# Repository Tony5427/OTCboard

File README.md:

# OTCboard

https://www.ckassoc.com/press-release/how-to-replace-a-hall-effect-sensor-with-a-tmr-sensor

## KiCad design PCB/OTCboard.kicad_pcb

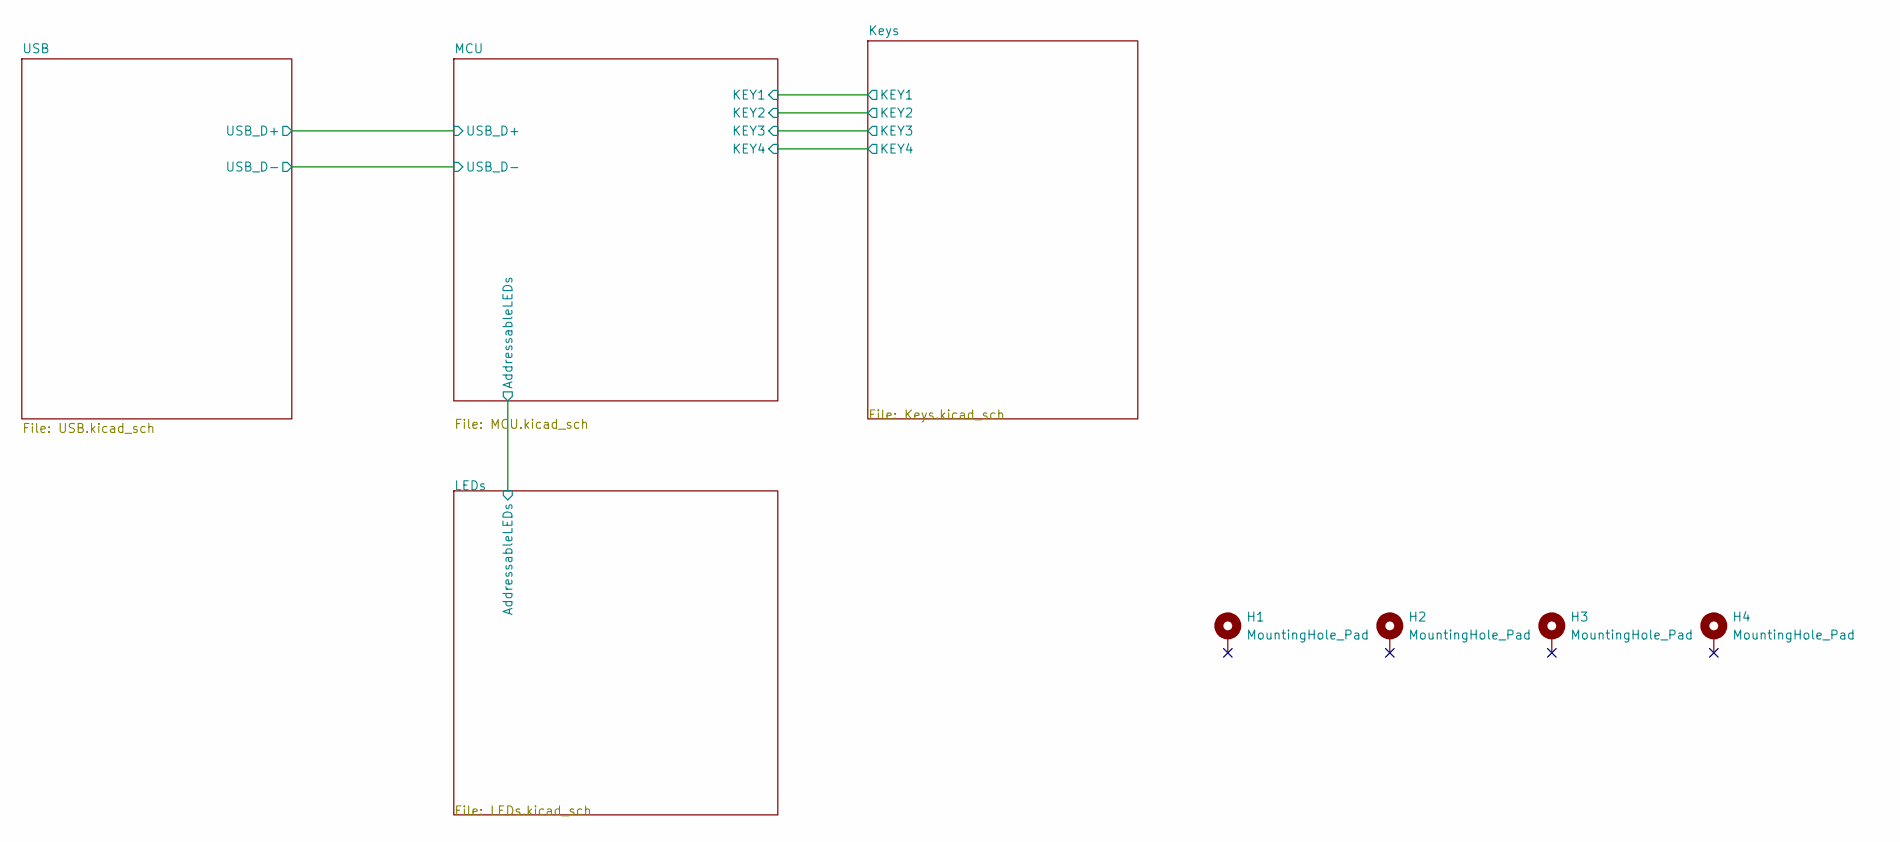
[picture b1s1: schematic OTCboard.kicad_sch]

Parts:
H1, H2, H3, H4: MountingHole_Pad; MountingHole_3.2mm_M3_Pad_TopBottom

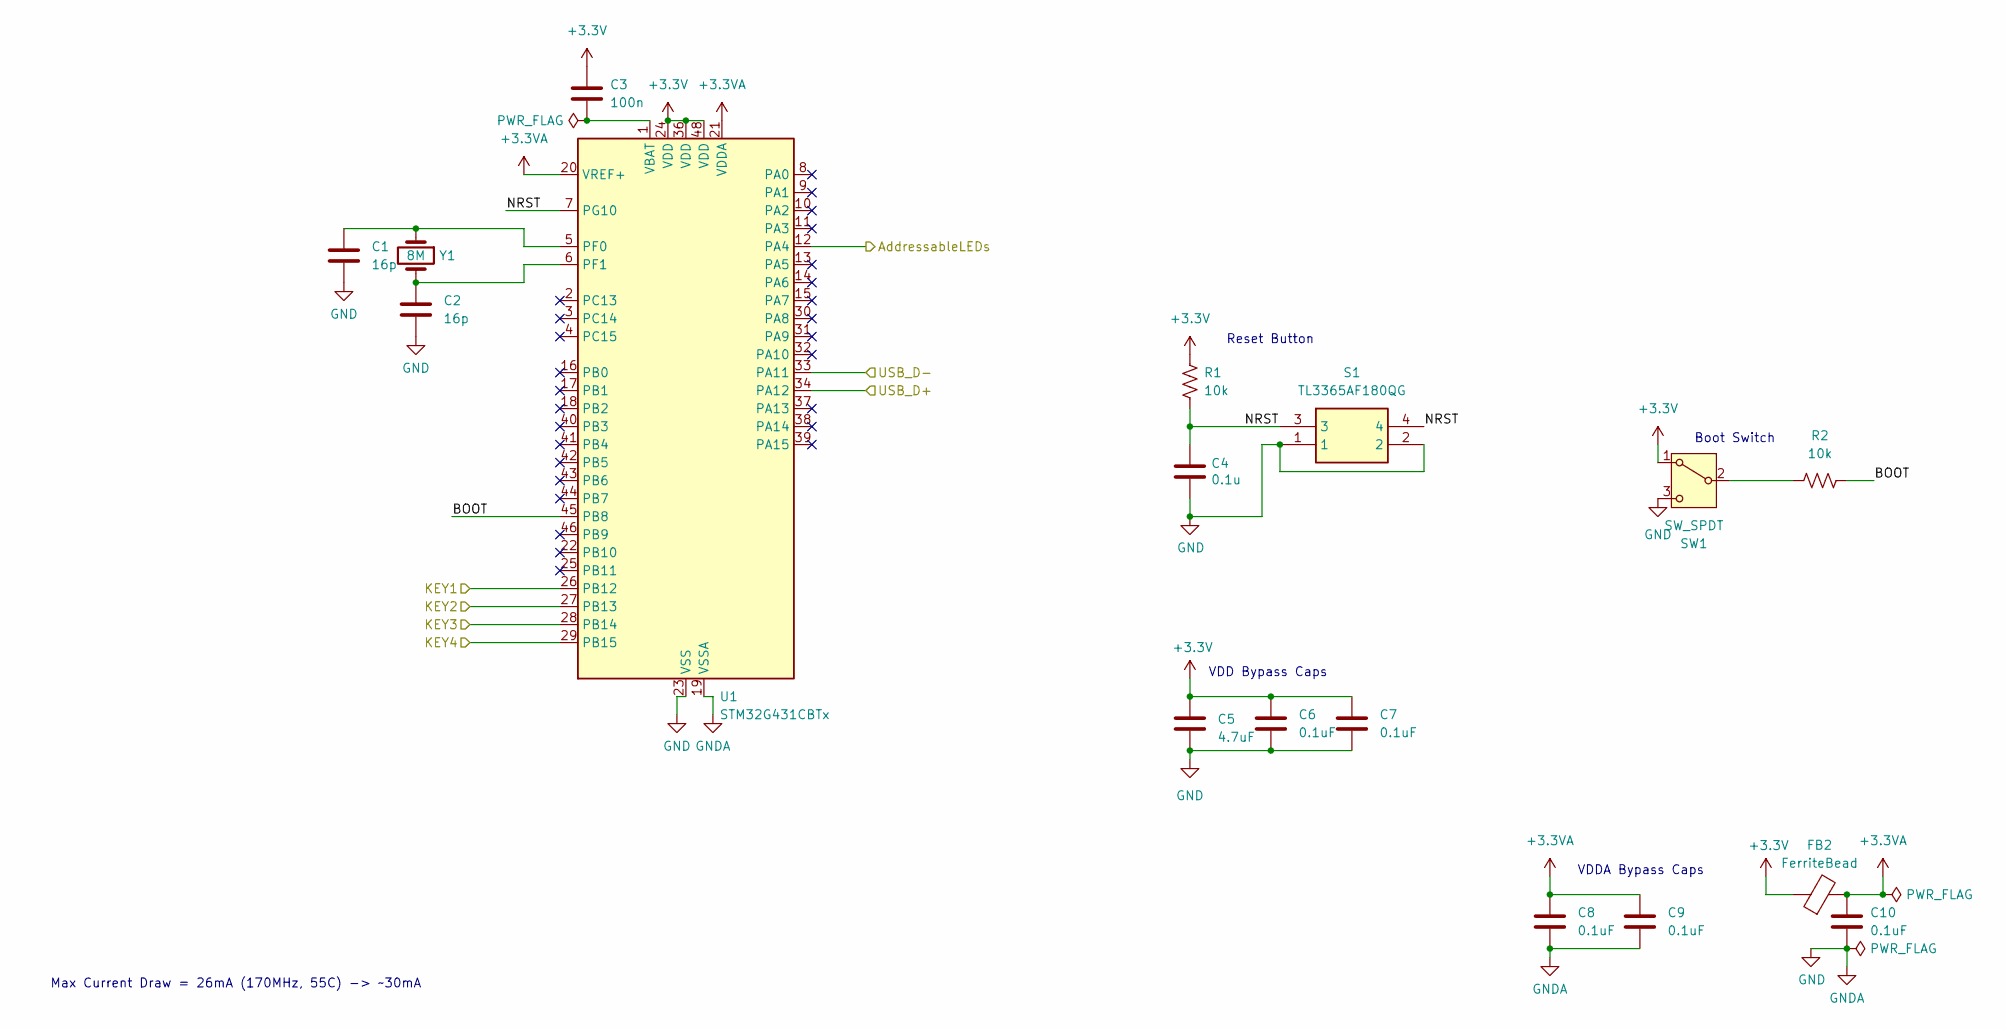
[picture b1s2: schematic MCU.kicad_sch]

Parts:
C1, C2: 16p; C_0603_1608Metric_Pad1.08x0.95mm_HandSolder
C3: 100n; C_0603_1608Metric_Pad1.08x0.95mm_HandSolder
C4: 0.1u; C_0603_1608Metric_Pad1.08x0.95mm_HandSolder; Mouser Part Number MLASH168SB7104KTNA01
C5: 4.7uF; C_0805_2012Metric_Pad1.18x1.45mm_HandSolder; Mouser Part Number 08055D475KAT4A
C6, C7, C8, C9, C10: 0.1uF; C_0603_1608Metric_Pad1.08x0.95mm_HandSolder; Mouser Part Number MLASH168SB7104KTNA01
FB2: FerriteBead; L_0603_1608Metric_Pad1.05x0.95mm_HandSolder; Mouser Part Number 704-MFBW1V2012-121-R
R1, R2: 10k; R_0603_1608Metric_Pad0.98x0.95mm_HandSolder; Mouser Part Number CRCW060310K0FKEI
S1: TL3365AF180QG; Mouser Part Number 612-TL3365AF180QG
SW1: SW_SPDT; CLSB12B01T; Mouser Part Number CJS-1200TA
U1: STM32G431CBTx; LQFP-48_7x7mm_P0.5mm
Y1: 8M; Crystal_SMD_Abracon_ABM3-2Pin_5.0x3.2mm; Mouser Part Number ABM3-8.000MHZ-D2Y-T

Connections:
+3.3V: C3.2, C5.1, C6.1, C7.1, FB2.1, R1.2, SW1.1 (A), U1.24 (VDD), U1.36 (VDD), U1.48 (VDD); also elsewhere on the board
+3.3VA: C8.1, C9.1, C10.1, FB2.2, U1.20 (VREF+), U1.21 (VDDA); also elsewhere on the board
/Keys/KEY1: U1.26 (PB12); also elsewhere on the board
/Keys/KEY2: U1.27 (PB13); also elsewhere on the board
/Keys/KEY3: U1.28 (PB14); also elsewhere on the board
/Keys/KEY4: U1.29 (PB15); also elsewhere on the board
/LEDs/AddressableLEDs: U1.12 (PA4); also elsewhere on the board
/MCU/BOOT: R2.1, U1.45 (PB8)
/MCU/NRST: C4.1, R1.1, S1.3, S1.4, U1.7 (PG10)
/USB/USB_D+: U1.34 (PA12); also elsewhere on the board
/USB/USB_D-: U1.33 (PA11); also elsewhere on the board
GND: C1.2, C2.1, C4.2, C5.2, C6.2, C7.2, C8.2, C9.2, C10.2, S1.1, S1.2, SW1.3 (C), U1.19 (VSSA), U1.23 (VSS), U1.35 (VSS), U1.47 (VSS); also elsewhere on the board
unnamed: R2.2, SW1.2 (B)
unnamed: C1.1, U1.5 (PF0), Y1.1
unnamed: C2.2, U1.6 (PF1), Y1.2
unnamed: C3.1, U1.1 (VBAT)

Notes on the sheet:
Reset Button
VDDA Bypass Caps
VDD Bypass Caps
Boot Switch
Max Current Draw = 26mA (170MHz, 55C) -> ~30mA

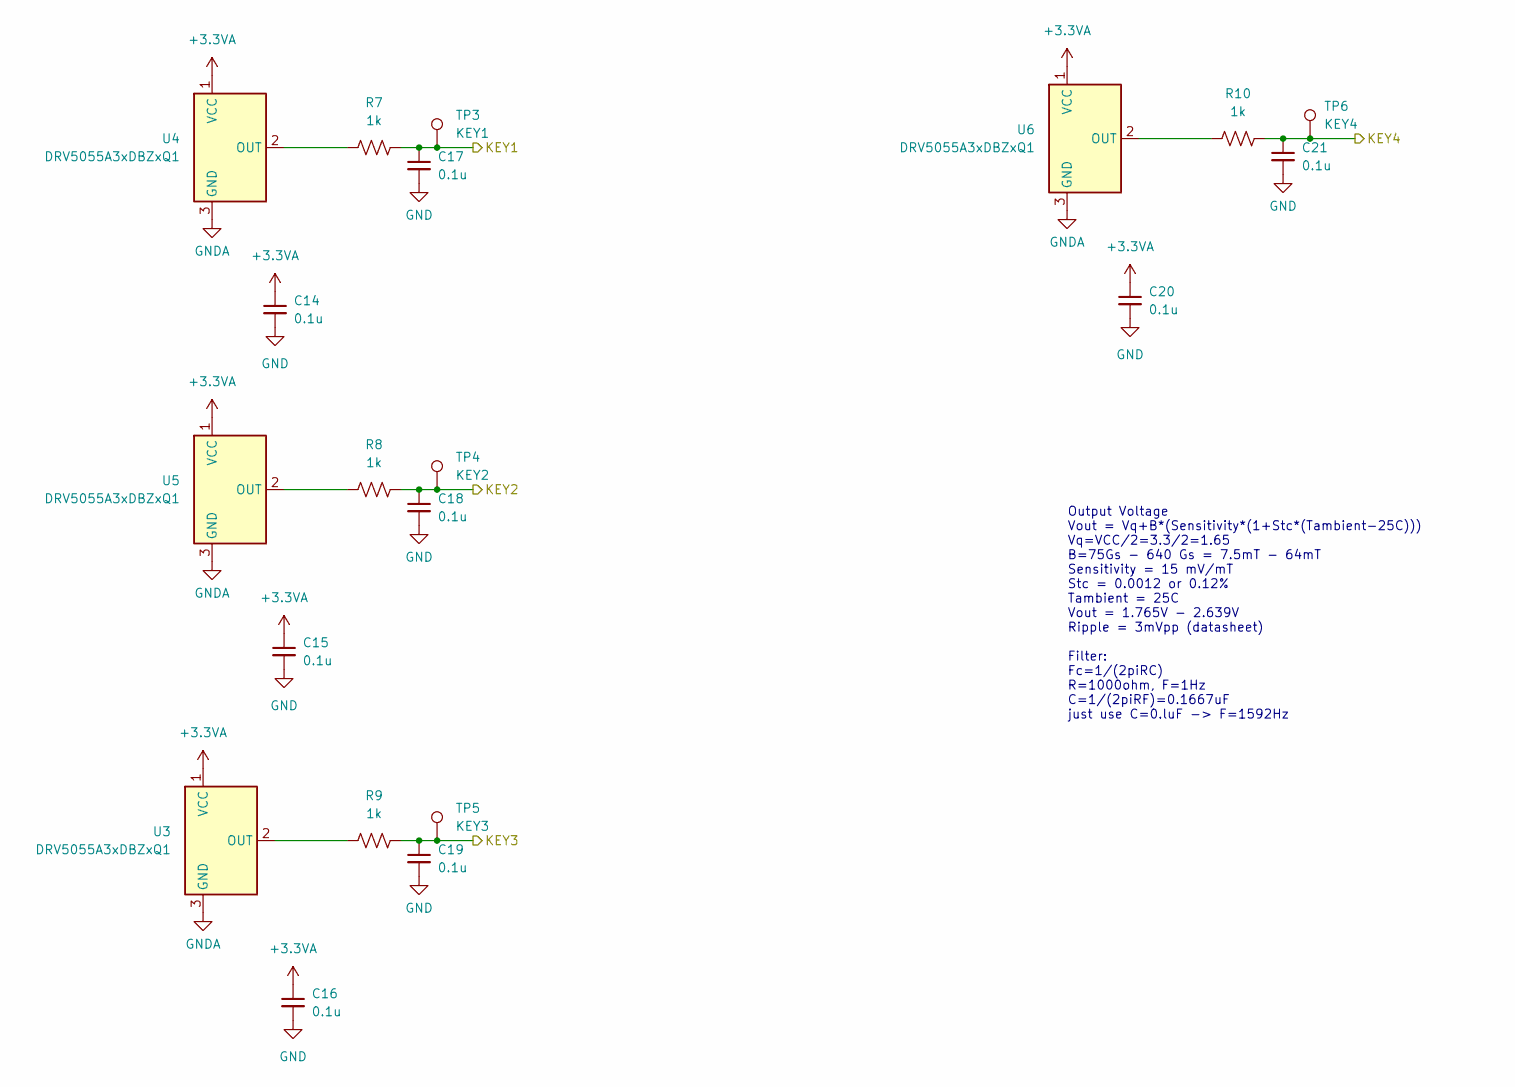
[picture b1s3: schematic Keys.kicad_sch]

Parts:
C14, C15, C16, C17, C18, C19, C20, C21: 0.1u; C_0603_1608Metric_Pad1.08x0.95mm_HandSolder
R7, R8, R9, R10: 1k; R_0603_1608Metric_Pad0.98x0.95mm_HandSolder
TP3: KEY1; TestPoint_Loop_D2.54mm_Drill1.5mm_Beaded
TP4: KEY2; TestPoint_Loop_D2.54mm_Drill1.5mm_Beaded
TP5: KEY3; TestPoint_Loop_D2.54mm_Drill1.5mm_Beaded
TP6: KEY4; TestPoint_Loop_D2.54mm_Drill1.5mm_Beaded
U3, U4, U5, U6: DRV5055A3xDBZxQ1; SOT-23

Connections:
+3.3VA: C14.1, C15.1, C16.1, C20.1, U3.1 (VCC), U4.1 (VCC), U5.1 (VCC), U6.1 (VCC); also elsewhere on the board
/Keys/KEY1: C17.1, R7.2, TP3.1; also elsewhere on the board
/Keys/KEY2: C18.1, R8.2, TP4.1; also elsewhere on the board
/Keys/KEY3: C19.1, R9.2, TP5.1; also elsewhere on the board
/Keys/KEY4: C21.1, R10.2, TP6.1; also elsewhere on the board
GND: C14.2, C15.2, C16.2, C17.2, C18.2, C19.2, C20.2, C21.2, U3.3 (GND), U4.3 (GND), U5.3 (GND), U6.3 (GND); also elsewhere on the board
unnamed: R9.1, U3.2 (OUT)
unnamed: R7.1, U4.2 (OUT)
unnamed: R8.1, U5.2 (OUT)
unnamed: R10.1, U6.2 (OUT)

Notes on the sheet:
Output Voltage Vout = Vq+B*(Sensitivity*(1+Stc*(Tambient-25C))) Vq=VCC/2=3.3/2=1.65 B=75Gs - 640 Gs = 7.5mT - 64mT Sensitivity = 15 mV/mT Stc = 0.0012 or 0.12% Tambient = 25C Vout = 1.765V - 2.639V Ripple = 3mVpp (datasheet) Filter: Fc=1/(2piRC) R=1000ohm, F=1Hz C=1/(2piRF)=0.1667uF just use C=0.lu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

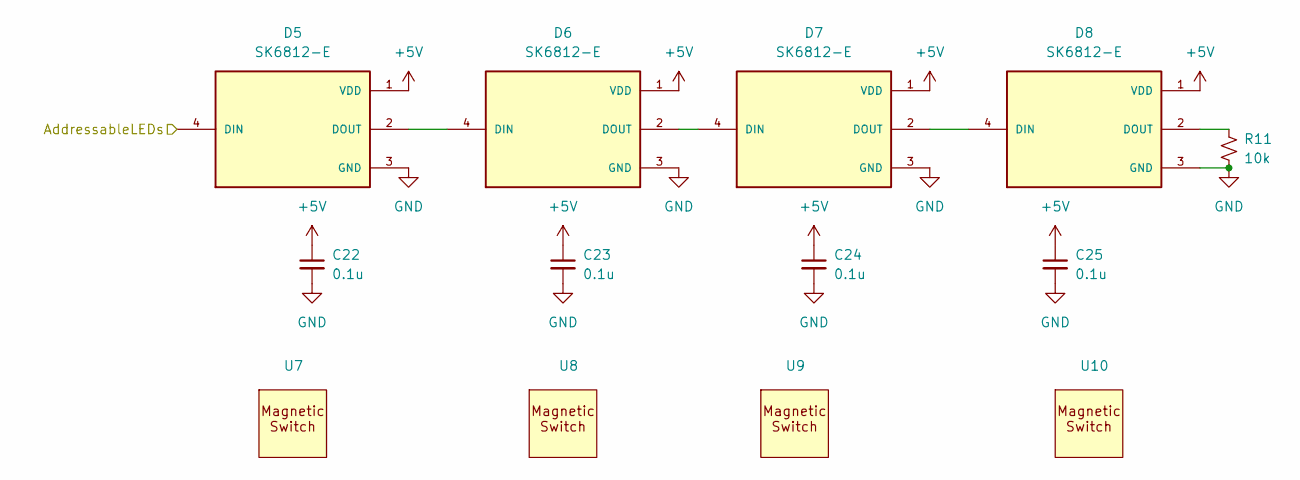
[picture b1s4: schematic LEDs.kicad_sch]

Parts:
C22, C23, C24, C25: 0.1u; C_0603_1608Metric_Pad1.08x0.95mm_HandSolder
D5, D6, D7, D8: SK6812-E; LED_SK6812-E; PARTREV 2
R11: 10k; R_0603_1608Metric_Pad0.98x0.95mm_HandSolder
U7, U8, U9, U10: Cherry MX compatible

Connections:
+5V: C22.1, C23.1, C24.1, C25.1, D5.1 (VDD), D6.1 (VDD), D7.1 (VDD), D8.1 (VDD); also elsewhere on the board
/LEDs/AddressableLEDs: D5.4 (DIN); also elsewhere on the board
GND: C22.2, C23.2, C24.2, C25.2, D5.3 (GND), D6.3 (GND), D7.3 (GND), D8.3 (GND), R11.2; also elsewhere on the board
unnamed: D5.2 (DOUT), D6.4 (DIN)
unnamed: D6.2 (DOUT), D7.4 (DIN)
unnamed: D7.2 (DOUT), D8.4 (DIN)
unnamed: D8.2 (DOUT), R11.1

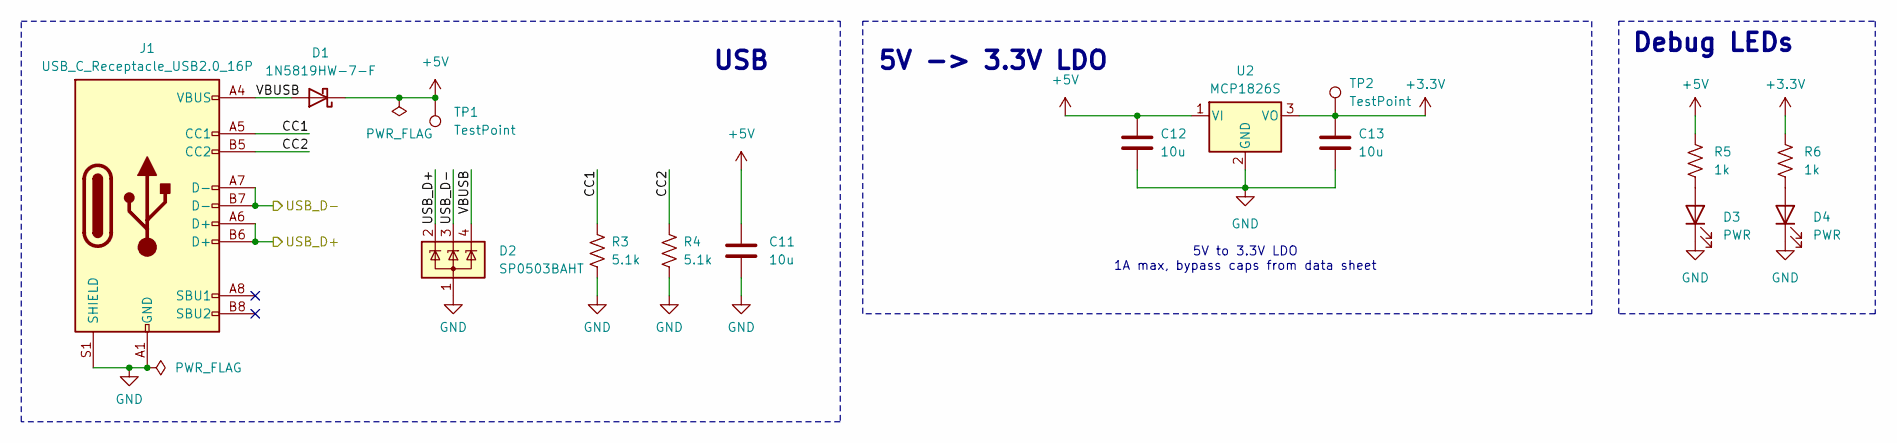
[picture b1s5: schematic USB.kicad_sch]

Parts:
C11, C12, C13: 10u; C_0805_2012Metric_Pad1.18x1.45mm_HandSolder; Mouser Part Number 81-GRM21BR61H106KE3K
D1: 1N5819HW-7-F; D_SOD-123; Mouser Part Number 621-1N5819HW-F
D2: SP0503BAHT; SOT-143
D3, D4: PWR; LED_0603_1608Metric_Pad1.05x0.95mm_HandSolder
J1: USB_C_Receptacle_USB2.0_16P; USB_C_Receptacle_GCT_USB4105-xx-A_16P_TopMnt_Horizontal
R3, R4: 5.1k; R_0603_1608Metric_Pad0.98x0.95mm_HandSolder
R5: 1k; R_0603_1608Metric_Pad0.98x0.95mm_HandSolder; Mouser Part Number 71-CRCW1206-470-E3
R6: 1k; R_0603_1608Metric_Pad0.98x0.95mm_HandSolder; Mouser Part Number 71-CRCW0603120RFKEC
TP1, TP2: TestPoint; TestPoint_Loop_D2.54mm_Drill1.5mm_Beaded
U2: MCP1826S; SOT-223-3_TabPin2

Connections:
+3.3V: C13.1, R6.1, TP2.1, U2.3 (VO); also elsewhere on the board
+5V: C11.1, C12.1, D1.1 (K), R5.1, TP1.1, U2.1 (VI); also elsewhere on the board
/USB/CC1: J1.A5 (CC1), R3.1
/USB/CC2: J1.B5 (CC2), R4.1
/USB/USB_D+: D2.2 (K), J1.A6 (D+), J1.B6 (D+); also elsewhere on the board
/USB/USB_D-: D2.3 (K), J1.A7 (D-), J1.B7 (D-); also elsewhere on the board
/USB/VBUSB: D1.2 (A), D2.4 (K), J1.A4 (VBUS), J1.A9 (VBUS), J1.B4 (VBUS), J1.B9 (VBUS)
GND: C11.2, C12.2, C13.2, D2.1 (A), D3.1 (K), D4.1 (K), J1.A1 (GND), J1.A12 (GND), J1.B1 (GND), J1.B12 (GND), J1.S1 (SHIELD), R3.2, R4.2, U2.2 (GND); also elsewhere on the board
unnamed: D3.2 (A), R5.2
unnamed: D4.2 (A), R6.2

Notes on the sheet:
Debug LEDs
5V -> 3.3V LDO
5V to 3.3V LDO 1A max, bypass caps from data sheet
USB

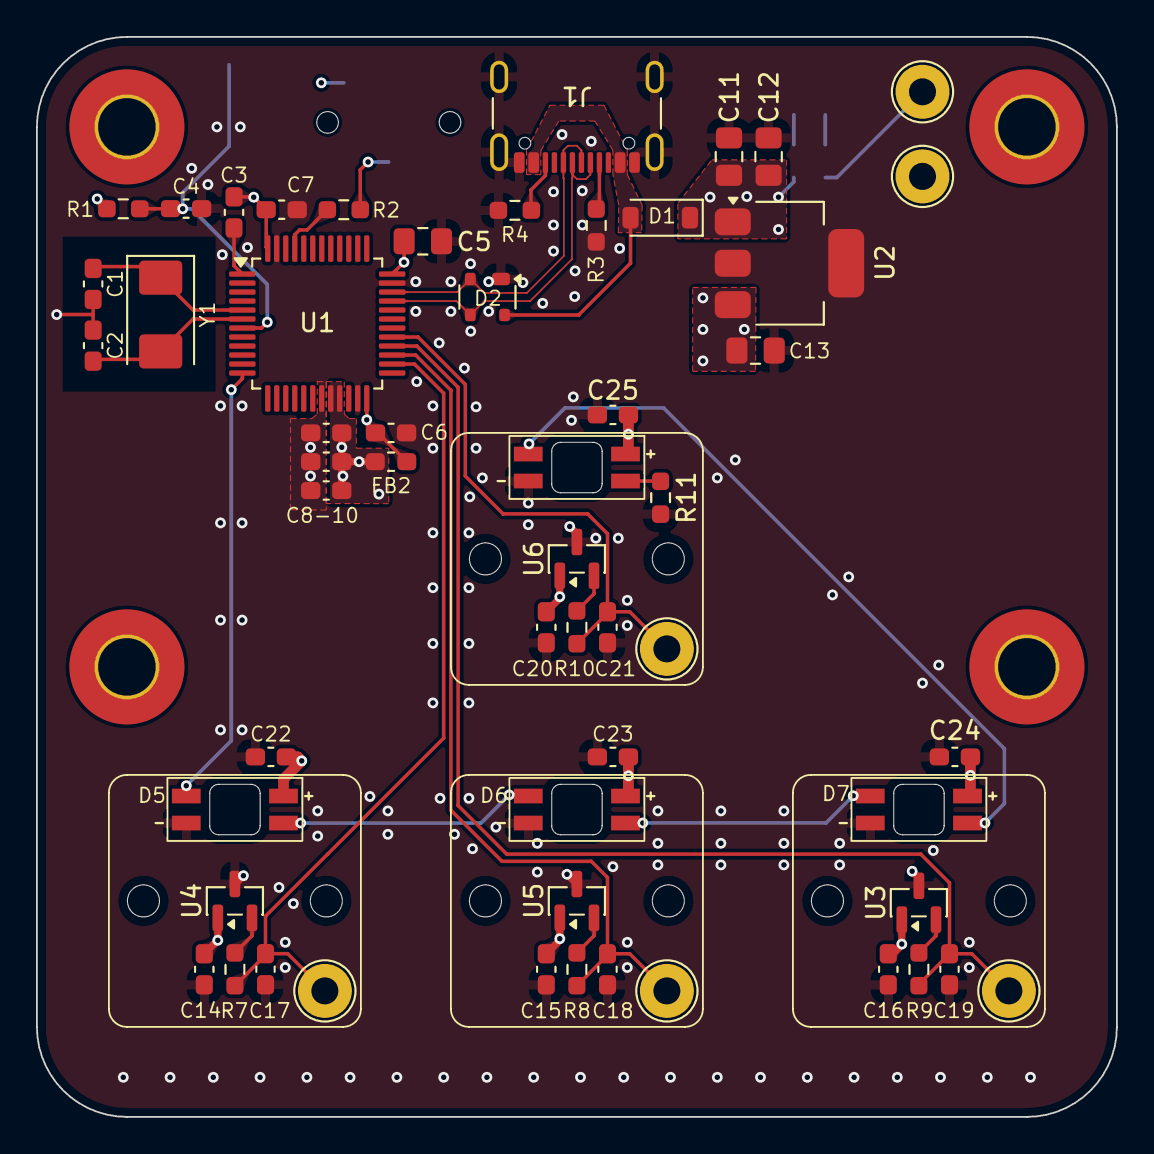
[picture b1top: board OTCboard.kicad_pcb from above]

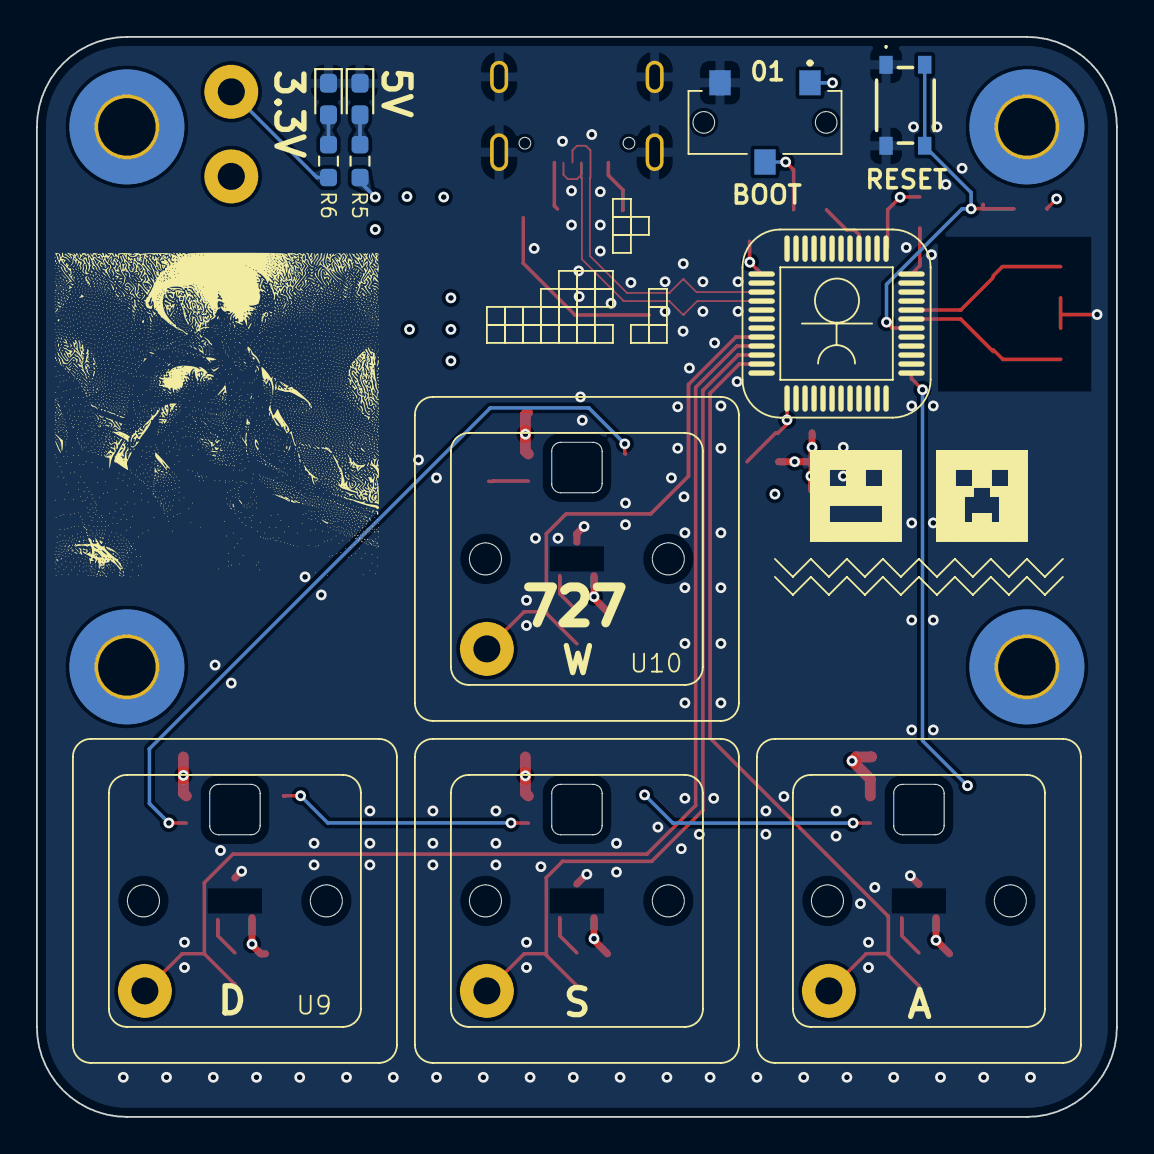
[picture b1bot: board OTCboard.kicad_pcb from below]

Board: 4 copper layers, 60.0 x 60.0 mm, 69 parts (10 on the bottom side), 30 nets.

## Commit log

2025-04-03 square
2025-11-10 starting work again
2025-11-25 kicad schematic pages
2025-12-20 switching to hall effect for now
2025-12-21 cramming for portfolio
2025-12-25 only need to find boot and reset footprints
2026-01-30 testing out g431
2026-03-21 removed udpliate pins sheet
2026-03-22 fixing this later
2026-05-11 changing to wasd
2026-05-26 new update
2026-06-01 schematic done?
2026-06-03 analog signal design research
2026-06-15 routing
2026-06-18 gerbers and added to cart on jlc
